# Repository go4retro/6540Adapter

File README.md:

# 6540Adapter
MOS 6540 to JEDEC 27XX(X) Adapter

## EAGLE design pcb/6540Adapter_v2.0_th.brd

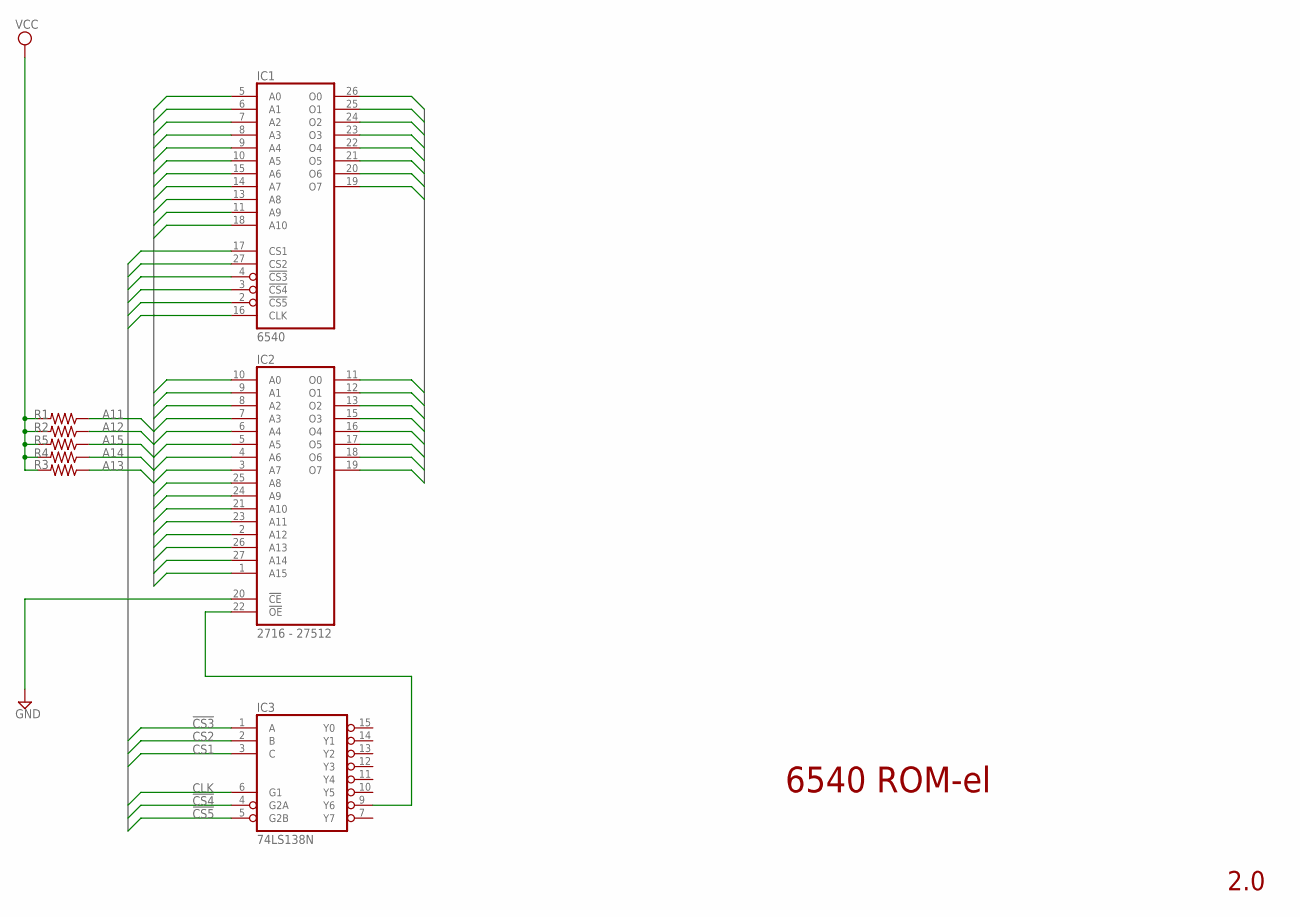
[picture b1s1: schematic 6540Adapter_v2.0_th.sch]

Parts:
IC1: 6540; DIL28-ROUNDPAD
IC2: 2716 - 27512; DIL28-ROUNDPAD
IC3: 74LS138N; DIL16
R1, R2, R3, R4, R5: R-US_0204/5; 0204/5

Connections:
!CS3: IC1.4 (!CS3), IC3.1 (A)
!CS4: IC1.3 (!CS4), IC3.4 (G2A)
!CS5: IC1.2 (!CS5), IC3.5 (G2B)
A0: IC1.5 (A0), IC2.10 (A0)
A1: IC1.6 (A1), IC2.9 (A1)
A2: IC1.7 (A2), IC2.8 (A2)
A3: IC1.8 (A3), IC2.7 (A3)
A4: IC1.9 (A4), IC2.6 (A4)
A5: IC1.10 (A5), IC2.5 (A5)
A6: IC1.15 (A6), IC2.4 (A6)
A7: IC1.14 (A7), IC2.3 (A7)
A8: IC1.13 (A8), IC2.25 (A8)
A9: IC1.11 (A9), IC2.24 (A9)
A10: IC1.18 (A10), IC2.21 (A10)
A11: IC2.23 (A11), R1.1
A12: IC2.2 (A12), R2.1
A13: IC2.26 (A13), R3.1
A14: IC2.27 (A14), R4.1
A15: IC2.1 (A15), R5.1
CLK: IC1.16 (CLK), IC3.6 (G1)
CS1: IC1.17 (CS1), IC3.3 (C)
CS2: IC1.27 (CS2), IC3.2 (B)
D0: IC1.26 (O0), IC2.11 (O0)
D1: IC1.25 (O1), IC2.12 (O1)
D2: IC1.24 (O2), IC2.13 (O2)
D3: IC1.23 (O3), IC2.15 (O3)
D4: IC1.22 (O4), IC2.16 (O4)
D5: IC1.21 (O5), IC2.17 (O5)
D6: IC1.20 (O6), IC2.18 (O6)
D7: IC1.19 (O7), IC2.19 (O7)
GND: IC1.1 (GND), IC2.14 (GND), IC2.20 (!CE), IC3.8 (GND)
unnamed: IC2.22 (!OE), IC3.9 (Y6)
VCC: IC1.12 (VCC), IC2.28 (VCC), IC3.16 (VCC), R1.2, R2.2, R3.2, R4.2, R5.2

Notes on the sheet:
6540 ROM-el
2.0

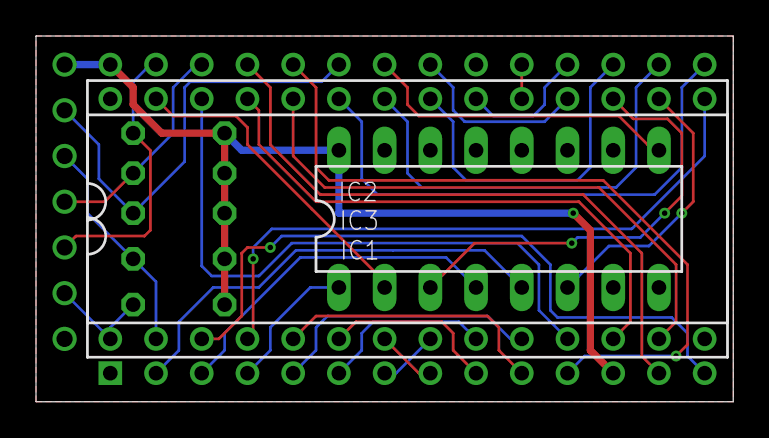
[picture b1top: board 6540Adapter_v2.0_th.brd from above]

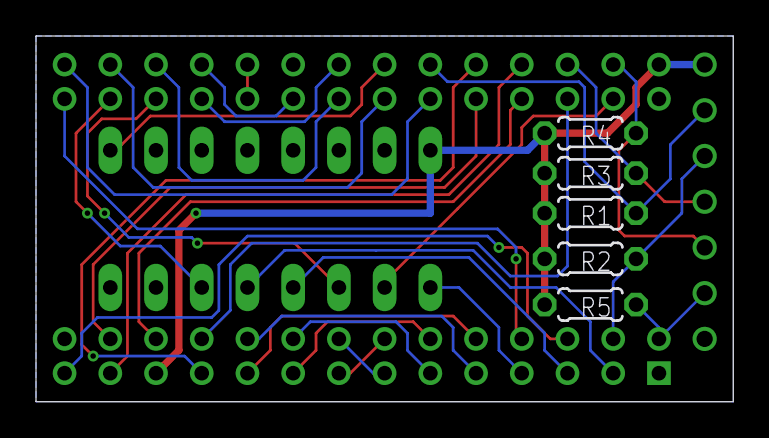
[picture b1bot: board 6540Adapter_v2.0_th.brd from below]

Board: 2 copper layers, 38.7 x 20.3 mm, 8 parts (5 on the bottom side), 33 nets.

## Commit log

2018-03-11 Updated license
2018-03-11 Added README.md
2020-05-27 Pics and Gerbers
2020-10-11 PCB Updates and BOM cleanup

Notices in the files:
pcb/6540Adapter_v2.0_th.brd:
(c)2012 RETRO Innovations
